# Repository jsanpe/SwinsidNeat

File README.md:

# Nano SwinSID Neat

Yet another PCB layout of the nano SwinSID focusing on aesthetics

*Note: The design was modified and the new PCB has not been fully tested. I will remove this note when I can get some PCBs with this new layout and test them myself.*

## What is this repo about?

A kicad implementation of the Swinsid Nano. Based on the `nano SwinSID b` design by Tolaemon (http://tolaemon.com/nss/), this implementation preserves the schematic but introduces changes in the PCB layout:
- All components are placed on the bottom layer: the goal is to leave the top layer component free and use the silkscreen to mimic the MOS 6581 logo. So, this new layout has aesthetic purposes only.

- The ICSP header is now gone ~~optional~~: Some of the pins on the side have been repurposed to program the ATMega without the need to add an additional 2x3 header, which contributes to a cleaner top. The required connections are marked in the PCB

| ICSP Pin | Swinsid Pin | Silkscreen Mark |
|----------|-------------|-----------------|
| 1 - Miso | Pin 1 |Mi|
| 2 - Vcc  | Pin 25 |5v|
| 3 - Sck  | Pin 7 |Sck|
| 4 - Mosi | Pin 4 |Mo|
| 5 - Reset| Pin 5 |Rs|
| 6 - Gnd  | Pin 14| G|

- The LED is placed on the top layer, mostly for visibility reasons (in daylight conditions it is easier to spot the led to verify power is reaching the swinsid). However, the led is fully optional allowing the top layer to only have the silkscreen.

Other than these two minor changes, the design is the exact same as Tolaemon's, so all credits go to him and, of course, the original creator of the Swinsid Nano (x1541 ~ http://www.nightfallcrew.com/27/02/2011/nanoswinsid-pcb-by-x1541/) and its predecessors.

## BOM
| Comment	| Designator |	Footprint |
|---------|------------|------------|
| 100n	| C1 |	SMD 0603 |
| LED	  |  D1|	LED_0603 |
|Conn_PIC_ICSP_ICD|	J1	| PinHeader_2x03_P2.54mm_Vertical |
|Jumper |	JP1,JP2	| PinHeader_1x02_P2.54mm_Vertical |
|2k2	|R1	|SMD 0603|
|4k7	|R3	|SMD 0603|
|1k	|R2,R4	|SMD 0603|
|240k	|R5	|SMD 0603|
|330	|R6	|SMD 0603|
|ATmega88PA-AU	|U1	|TQFP-32_7x7mm_P0.8mm|
|SG-7050CAN 32Mhz|	X1	|Crystal_SMD_7050-4Pin_7.0x5.0mm|

## Jumpers
- JP1: Selects emulation mode. Leave open for 8580, and close for 6581
- JP2: Selects output voltage. Leave open for mainboards designed for 6581 (this resistor is already in the mainboard), and close for mainboards designed for 8580.

My personal preference is to permanently solder the pads instead of placing a jumper for aesthetic reasons. Feel free to do otherwise.

## Firmware
Please refer to Toalemon's [guide](http://tolaemon.com/nss/) for additional information on available firmwares and how to flash them in the ATMega MPU.

## License
Given the incremental nature of this design, the original licenses of the Nano SwinSID and Nano SwinSIDb apply to this repo. I have not been able to clearly identify what licenses these original designs have, so in the absence of any additional info the current repo has been released under a MIT license. Please contanct me or open an issue in github if you have additional information about licensing that should be included.

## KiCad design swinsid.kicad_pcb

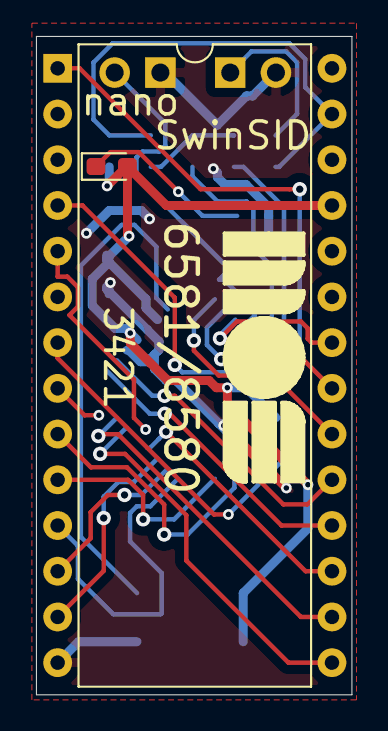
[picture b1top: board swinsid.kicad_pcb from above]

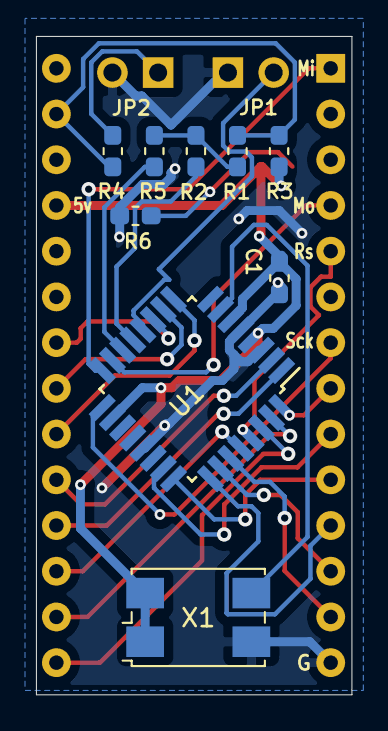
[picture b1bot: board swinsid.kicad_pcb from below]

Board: 2 copper layers, 17.5 x 36.6 mm, 13 parts (11 on the bottom side), 28 nets.

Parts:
C1: 100n; C_0603_1608Metric_Pad1.05x0.95mm_HandSolder
D1: LED; LED_0603_1608Metric_Pad1.05x0.95mm_HandSolder
JP1, JP2: Jumper; PinHeader_1x02_P2.54mm_Vertical
R1: 2k2; R_0603_1608Metric_Pad1.05x0.95mm_HandSolder
R2, R4: 1k; R_0603_1608Metric_Pad1.05x0.95mm_HandSolder
R3: 4k7; R_0603_1608Metric_Pad1.05x0.95mm_HandSolder
R5: 240k; R_0603_1608Metric_Pad1.05x0.95mm_HandSolder
R6: 330; R_0603_1608Metric_Pad1.05x0.95mm_HandSolder
U1: ATmega88PA-AU; TQFP-32_7x7mm_P0.8mm
U2: SID6581; DIP-28_W15.24mm
X1: SG-7050CAN; Crystal_SMD_7050-4Pin_7.0x5.0mm

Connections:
+5V: C1.1, D1.2, R3.2, U1.4, U1.6, U1.18, U2.25, X1.1, X1.4
A0: U1.23, U2.9
A1: U1.24, U2.10
A2: U1.25, U2.11
A3: U1.26, U2.12
A4: U1.27, U2.13
AUDIO1: R2.2, U1.13
AUDIO2: R5.2, U1.14
CS: U1.32, U2.8
D0: U1.30, U2.15
D1: U1.31, U2.16
D2: U1.28, U2.17
D3: U1.1, U2.18
D4: U1.2, U2.19
D5: U1.9, U2.20
D6: U1.10, U2.21
D7: U1.11, U2.22
GND: C1.2, JP1.1, JP2.2, R6.2, U1.3, U1.5, U1.21, U2.14, X1.2
MISO: U1.16, U2.1
MOSI: U1.15, U2.4
unnamed: D1.1, R6.1
unnamed: JP2.1, R4.2
unnamed: R1.1, R3.1, R4.1, U2.27
unnamed: R1.2, R2.1, R5.1
RESET: U1.29, U2.5
RW: U1.17, U2.7
SELECT: JP1.2, U1.12
XTAL1: U1.7, X1.3

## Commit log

2021-08-24 Initial Release
2021-08-25 Add image to readme file
2021-08-26 More images
2021-08-26 Reduce image size
2021-08-29 New layout without C logo Remove ICSP 2x3 header for better layout Rotate MCU for better layout
2021-08-29 Update gerbers
2021-08-29 new images for readme
2021-08-30 Change mask color in front image
2021-12-07 Updated swinsid image
